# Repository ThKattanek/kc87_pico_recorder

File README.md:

# KC87 Pico Recorder

KC87 Kassetten-Recorder Emulator mit Raspberry Pi Pico (RP2040) oder Pico 2 (RP2350).

## Status

**✅ Recording (Aufnahme): funktional**  
**✅ Auswertung am PC: Blöcke, Prüfsummen, BASIC-Programmname, TAP-Export** (in JKCEMU geladen und gestartet)  
✅ Playback (Wiedergabe): TAP/CSV → Pico → KC87, BASIC-Programme (auch mit 72 Blöcken aus einer WAV-Datei) wurden am echten KC87 geladen

## Projektstruktur

```
kc87_pico_recorder/
├── firmware/            Pico-Firmware (C, Pico SDK, PIO)
├── pc_commandline_tool/ PC-Kommandozeilentool kc87tool (C++17)
├── hardware/            KiCad-Schaltplan & PCB
├── doc/                 Dokumentation
├── PROTOCOL.md          Protokoll-Dokumentation
└── README.md
```

## Hardware

- Raspberry Pi Pico (RP2040) oder Pico 2 (RP2350), optional mit Debug-Probe
- **GPIO 2**: Eingang für das KC87-Signal (KC87 → Pico, Programm-Save)
- **GPIO 3**: Playback-Ausgang (`PLAY_SIGNAL_PICO` — Pico → KC87)

Maßgeblich für die Pinbelegung ist der Schaltplan in `hardware/`.

## Firmware

- Quellen: `firmware/main.c`, `firmware/pulse_timer.pio` (Target `kc87_logger`)
- Ein PIO-Zustandsautomat misst abwechselnd die Dauer der High- und Low-Phasen an GP2
- Timing-Auflösung: 0,2 µs (5 MHz Zähltakt, 32-Bit-Zähler)
- Die Messwerte laufen per DMA in einen 32-KB-Ringpuffer; daher gehen auch bei kurzen USB-Verzögerungen keine Pulse verloren
- Übertragung über USB-CDC (siehe [PROTOCOL.md](PROTOCOL.md))
- Gesteuert vom PC: `S` startet die Aufnahme, `X` beendet sie, `P` startet die Wiedergabe
- Wiedergabe: der PC schickt die Pulsdauern, ein PIO-Programm (`firmware/pulse_out.pio`, 0,2 µs Auflösung) gibt sie an GP3 aus. Der Pico sammelt zuerst 2048 Pulse vor, die USB-Verbindung bremst den PC, wenn der Puffer voll ist. Am Ende bleibt der Ausgang auf Low.

### Protokoll (Kurzfassung)

Alle Wörter sind `uint32` little-endian:

| Richtung | Inhalt |
|----------|--------|
| PC → Pico | `'S'` Start, `'X'` Stopp |
| Pico → PC | Header: `"KC87"` (`0x3738434B`), `tick_hz` |
| Pico → PC | Daten: Dauer in Ticks, abwechselnd High, Low, High, … |
| Pico → PC | Ende: `0xFFFFFFFF`, Status, Anzahl Werte |
| PC → Pico | `'P'` Wiedergabe: Pico antwortet mit dem Header, dann sendet der PC die Dauern und `0xFFFFFFFF` (Details in [PROTOCOL.md](PROTOCOL.md)) |

Status: Bit 0 = Ringpuffer-Überlauf, Bit 1 = PIO-Stall.

### Test-Firmware für den PLAY-Pegel

`firmware/play_test.c` (Target `kc87_play_test`, eigene `.uf2`-Datei) gibt an GPIO 3 ein Rechtecksignal mit 50 % Tastverhältnis aus. Damit lässt sich der Pegel der PLAY-Schaltung einstellen, noch ohne Playback-Software: PLAY_SIGNAL mit dem Oszilloskop messen und mit RV2 auf ca. 250 mV PP abgleichen (Einstellbereich ca. 165 bis 250 mV PP) (KC87-Eingang: Re = 10 kΩ, mind. 24 mV PP). Die Frequenzen sind die Sollwerte des KC87 (laut [Kassetteninterface](https://hc-ddr.hucki.net/wiki/doku.php/z9001/software/os/kassetteninterface)); am echten KC87 habe ich etwas niedrigere Werte gemessen (siehe [Bandformat](#bandformat)). Nach dem Start läuft der Wechsel zwischen 1,2 und 2,4 kHz (je 1 s).

Steuerung über die USB-Schnittstelle (z. B. mit `picocom -b 115200 /dev/ttyACM0` oder einem anderen Terminalprogramm), ein Zeichen genügt:

| Zeichen | Ausgabe |
|---------|---------|
| `1` | 1200 Hz (Bit 1) |
| `2` | 2400 Hz (Bit 0) |
| `3` | 600 Hz (Trennzeichen) |
| `a` | 1200 Hz und 2400 Hz im Wechsel, je 1 s |
| `0` | Ausgang aus (Low) |
| `h` | Hilfe |

## PC-Tool: kc87tool

Quelle: `pc_commandline_tool/kc87tool.cpp` (Windows, Linux, macOS).

```bash
kc87tool record <port> [--sec 30] [--out aufnahme]   # z.B. COM5 oder /dev/ttyACM0
kc87tool analyze <datei.csv>                          # Statistik
kc87tool decode <datei.csv> [--tap datei.tap]         # Blöcke + Programmname, optional TAP-Datei
kc87tool wav <datei.csv> [--rate 44100]               # Rechtecksignal als WAV
kc87tool encode <datei.tap> [--out datei.csv]         # TAP -> Pulsfolge
kc87tool fromwav <datei.wav> [--out datei.csv]        # WAV-Aufnahme -> Pulsfolge
kc87tool play <port> <datei.csv|.tap|.wav>            # über den Pico an den KC87 ausgeben
```

- **record**: sendet `S`, zeichnet `--sec` Sekunden auf (Standard 30), sendet `X` und speichert die Pulse als `<out>.csv`. Danach werden automatisch `analyze` und `decode` ausgeführt; dabei entsteht auch `<out>.tap`. Meldet Ringpuffer-Überlauf, PIO-Stall oder fehlenden Endmarker als Warnung.
- **analyze**: gibt Min/Median/Max für High, Low und Periodendauer aus, sowie die häufigsten Periodenlängen.
- **decode**: zerlegt das Bandsignal in Bytes und Blöcke (siehe [Bandformat](#bandformat)). Zeigt je Block Nummer und Prüfsummen-Status, bei BASIC-Programmen auch den Programmnamen. Mit `--tap <datei>` werden alle Blöcke mit gültiger Prüfsumme als TAP-Datei geschrieben, damit sie in einem Emulator geladen werden können (mit JKCEMU 0.9.9.1 getestet: laden und starten funktioniert). Blöcke mit falscher Prüfsumme werden übersprungen.
- **wav**: erzeugt `<name>.wav` (8 Bit, Mono) aus der CSV-Datei.
- **encode**: wandelt eine TAP-Datei in die Pulsfolge um, wie der KC87 sie auf Band schreibt (Vorton, Trennzeichen, Bytes, Prüfsumme). Zur Kontrolle lässt sich das Ergebnis mit `decode` wieder zurücklesen.
- **fromwav**: liest eine WAV-Aufnahme (PCM 8/16/24/32 Bit oder Float32, bei mehreren Kanälen der erste) und wandelt sie in die Pulsfolge um. Die Nulldurchgänge werden mit Hysterese gesucht und zwischen den Abtastwerten interpoliert, dadurch reichen auch niedrige Abtastraten. Die Polarität ist egal. Mit `decode --tap` lässt sich daraus eine TAP-Datei machen.
- **play**: sendet eine `.tap`-, `.wav`- oder `.csv`-Datei an den Pico, der sie an GPIO 3 ausgibt. Vorher am KC87 den Ladevorgang starten (z. B. `CLOAD`/`LOAD`). Die Wiedergabe dauert so lange wie die Originalaufnahme (der erste Vorton allein ca. 5,5 s). Warnt bei Pufferunterlauf oder Abbruch. Bei WAV-Dateien hängt `play` am Ende einen kurzen Vorton an, damit der KC87 den letzten Block abschließt.

CSV-Format: Kopfzeile `level;dauer_us`, danach je Zeile `1;<µs>` (High) oder `0;<µs>` (Low).

Beispielausgabe von `decode`:

```
Dekodiert: 260 Bytes, 2 Bloecke
  Block   0: Pruefsumme OK
  Block   1: Pruefsumme OK  BASIC-Programm "TEST123"
TAP geschrieben: aufnahme.tap (2 Bloecke)
```

### Bandformat

Aus einer echten `CSAVE`-Aufnahme abgelesen:

| Symbol | Periode | Frequenz |
|--------|---------|----------|
| Bit 0 | 2 Pulse à ca. 250 µs | ca. 2 kHz |
| Bit 1 | 2 Pulse à ca. 455 µs | ca. 1,1 kHz |
| Trennzeichen | 2 Pulse à ca. 870 µs | ca. 575 Hz |

Sollwerte laut [Kassetteninterface](https://hc-ddr.hucki.net/wiki/doku.php/z9001/software/os/kassetteninterface): Trennzeichen 600 Hz, 1-Bit 1200 Hz, 0-Bit 2400 Hz. Die gemessenen Werte liegen 5 bis 16 % darunter. Die Wiki-Tabelle ordnet 0- und 1-Bit umgekehrt zu; in den Aufnahmen ist die längere Periode das 1-Bit (nur so stimmen Prüfsummen und `D3 D3 D3`).

- Ein Byte besteht aus 8 Bits, LSB zuerst. Vor jedem Byte steht ein Trennzeichen.
- Vor jedem Block steht ein Vorton aus 1-Bits (der erste ist sehr lang, ca. 6000 Perioden).
- Ein Block hat 130 Bytes: Blocknummer, 128 Datenbytes, Prüfsumme (Summe der Datenbytes modulo 256).
- BASIC-Programme (`CSAVE`) enthalten `D3 D3 D3`, danach den Programmnamen (8 Zeichen) und den Programmtext.
- Das TAP-Format: 16 Byte Kennung `\xC3KC-TAPE by AF. `, danach je Block Blocknummer + 128 Datenbytes.

Die Schwellen für die Unterscheidung liegen bei 350 µs und 650 µs pro Puls (Konstanten `SHORT_MAX_US` und `MID_MAX_US` in `kc87tool.cpp`).

## Build

### Firmware

Über die VS Code Pico-Extension oder manuell (Pico SDK 2.3.0, `PICO_SDK_PATH` setzen):

```bash
cd firmware
mkdir -p build && cd build
cmake ..
ninja          # oder: make
```

Ergebnis: `kc87_logger.uf2` / `.elf` (Aufnahme) und `kc87_play_test.uf2` / `.elf` (PLAY-Test).

Die Ziel-Platine steht in `firmware/CMakeLists.txt` (`set(PICO_BOARD pico ...)`):

- Pico 1 (RP2040): `pico` (Standard)
- Pico 2 (RP2350): `pico2`, oder beim Konfigurieren mit `cmake -DPICO_BOARD=pico2 ..` (bei einem schon vorhandenen `build/`-Ordner diesen vorher löschen)

### PC-Tool

```bash
cd pc_commandline_tool
cmake -S . -B build
cmake --build build
```

Alternativ ohne CMake: `g++ -std=c++17 -O2 -o kc87tool kc87tool.cpp` (unter Windows mit MinGW/MSYS2 bzw. `cl /std:c++17 /O2 /EHsc kc87tool.cpp` mit Visual Studio).

## Workflow

1. **Pico flashen**: Firmware kompilieren → über Debug-Probe oder UF2 flashen
2. **Aufnahme starten**: `kc87tool record /dev/ttyACM0 --sec 30 --out aufnahme`
3. **Programm-Save am KC87 starten** (Signal an GPIO 2)
4. **Auswerten**: Analyse und Dekodierung laufen nach der Aufnahme automatisch; später erneut mit `kc87tool analyze aufnahme.csv` und `kc87tool decode aufnahme.csv --tap aufnahme.tap`
5. **Im Emulator laden**: die erzeugte `.tap`-Datei (z. B. in JKCEMU)
6. **Auf den KC87 laden**: Pegel mit `kc87_play_test` einstellen, am KC87 den Ladevorgang starten, dann `kc87tool play /dev/ttyACM0 aufnahme.tap`

## Bekannte Einschränkungen

- Playback ist am echten KC87 mit einem kurzen BASIC-Programm und mit einer WAV-Datei des Programms AIRWOLF (BASIC, 72 Blöcke, ca. 80 s) getestet, jeweils über `CLOAD`. Maschinencode ist ebenfalls getestet: der Zusatz-Monitor ZM30 (33 Blöcke, Original der Kassette R0112) und ein selbst geschriebenes Z80-Programm wurden geladen, das eigene Programm zusätzlich mit `P` im ZM30 gespeichert, aufgenommen und wieder zurückgespielt. Die Pulsdauern und Vorton-Längen stammen aus der Aufnahme. Nach dem letzten Block hängt `encode` einen kurzen Vorton an, weil der KC87 den Block erst mit der nächsten Flanke abschließt. Bei `.csv`-Dateien kommt das Ende aus der Aufnahme.
- Die Aufnahmedauer wird vom PC festgelegt (`--sec`), es gibt keinen automatischen Stopp nach Inaktivität
- Aufgenommen und geprüft sind bisher ein `CSAVE`-Programm (BASIC) und ein Maschinenprogramm, gespeichert mit `P` im ZM30. Bei Maschinencode-Dateien zeigt `decode` im Kopfblock (Block 0) Name, Typ und die drei Adressen an. Die Zuordnung der Adress-Felder ist aus ZM30 und der eigenen Aufnahme abgeleitet. Der letzte Block einer Datei trägt die Nummer 255.
- Als Exportformat gibt es nur TAP (mit JKCEMU 0.9.9.1 getestet, mit einem BASIC-Programm). Die Formate KCC und SSS gibt es nicht.
- Der Ringpuffer fasst 8192 Messwerte; bei sehr hoher Pulsrate und blockierter USB-Verbindung kann er überlaufen (Status-Bit 0)

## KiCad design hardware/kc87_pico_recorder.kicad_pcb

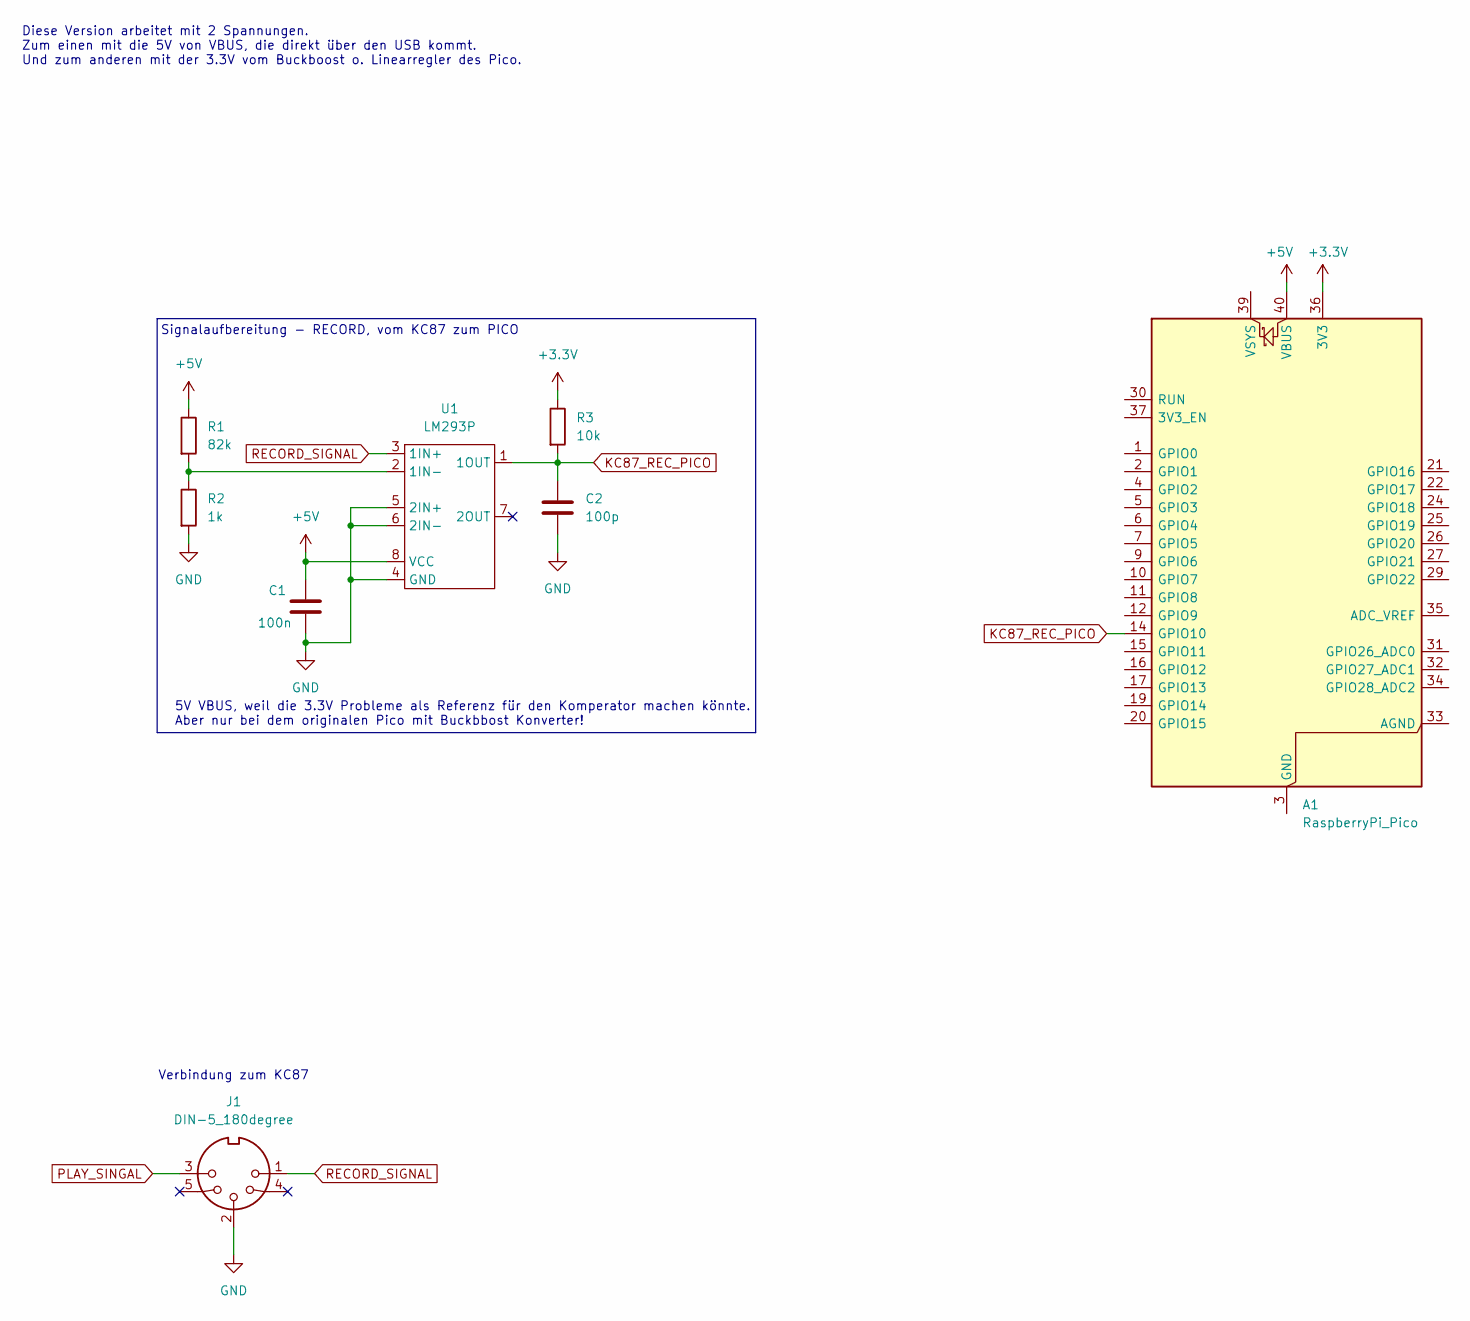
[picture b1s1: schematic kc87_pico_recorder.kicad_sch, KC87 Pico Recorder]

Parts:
A1: RaspberryPi_Pico; RaspberryPi_Pico_Common_SMD
C1: 100n; C_0805_2012Metric_Pad1.18x1.45mm_HandSolder
C2: 100p; C_0805_2012Metric_Pad1.18x1.45mm_HandSolder
J1: DIN-5_180degree; din-5
R1: 82k; R_0805_2012Metric_Pad1.20x1.40mm_HandSolder
R2: 1k; R_0805_2012Metric_Pad1.20x1.40mm_HandSolder
R3: 10k; R_0805_2012Metric_Pad1.20x1.40mm_HandSolder
U1: LM293P; DIP-8_W7.62mm_SMDSocket_SmallPads

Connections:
+3.3V: A1.36 (3V3), R3.1
+5V: A1.40 (VBUS), C1.1, R1.1, U1.8 (VCC)
GND: C1.2, C2.2, J1.2, R2.2, U1.4 (GND), U1.5 (2IN+), U1.6 (2IN-)
KC87_REC_PICO: A1.14 (GPIO10), C2.1, R3.2, U1.1 (1OUT)
unnamed: A1.3 (GND), A1.8 (GND), A1.13 (GND), A1.18 (GND), A1.23 (GND), A1.28 (GND), A1.38 (GND)
unnamed: R1.2, R2.1, U1.2 (1IN-)
PLAY_SINGAL: J1.3
RECORD_SIGNAL: J1.1, U1.3 (1IN+)

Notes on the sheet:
Verbindung zum KC87
5V VBUS, weil die 3.3V Probleme als Referenz für den Komperator machen könnte. Aber nur bei dem originalen Pico mit Buckbbost Konverter!
Diese Version arbeitet mit 2 Spannungen. Zum einen mit die 5V von VBUS, die direkt über den USB kommt. Und zum anderen mit der 3.3V vom Buckboost o. Linearregler des Pico.
Signalaufbereitung - RECORD, vom KC87 zum PICO

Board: 2 copper layers, 8 parts (0 on the bottom side), 7 nets, no tracks yet.

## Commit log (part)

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2025-11-22 projekt start
2025-11-22 changed readme.md
2025-11-22 Add initial project files and setup for KC87 Pico Recorder
    - Create README with project structure and ToDo list
    - Add .gitignore for build artifacts
    - Configure VSCode settings and tasks for building and debugging
    - Implement main application logic in main.c
    - Include CMake configuration for project setup
    - Import Raspberry Pi Pico SDK for development
2025-11-22 Modify ToDo list for v0.1
    Updated ToDo list with new tasks for signal handling.
2025-11-22 Fix typo in ToDo list for protocol definition
2025-11-22 added the kc87_pico_recorder_de.odt and pdf
2025-11-22 added the hardware directory with the kicad project with schematic
2025-11-22 Refactor CMakeLists.txt to use consistent project name and board type
2025-11-23 Refactor project structure: replace main.c with kc87_pico_recorder.c, update CMakeLists.txt, and add config.h for GPIO configuration
2026-01-30 Implement serial capture tool with CMake configuration and README documentation
2026-01-31 firmware: hhe “tools” folder has been moved.
2026-01-31 docs: update README and add PROTOCOL documentation for serial capture tool and WAV file generation
2026-01-31 Update .gitignore and enhance README for cross-compilation setup; add MinGW toolchain file
2026-02-03 Hardware: change kc87_pico_recorder.kicad_sch (new amplifier)
2026-02-06 update firmware and tools with ai
2026-02-08 Added final tape signal capture implementation with serial_capture tool as bin or wav. Firmware is now ready for capture.
2026-02-12 Add firmware version and update main output message
